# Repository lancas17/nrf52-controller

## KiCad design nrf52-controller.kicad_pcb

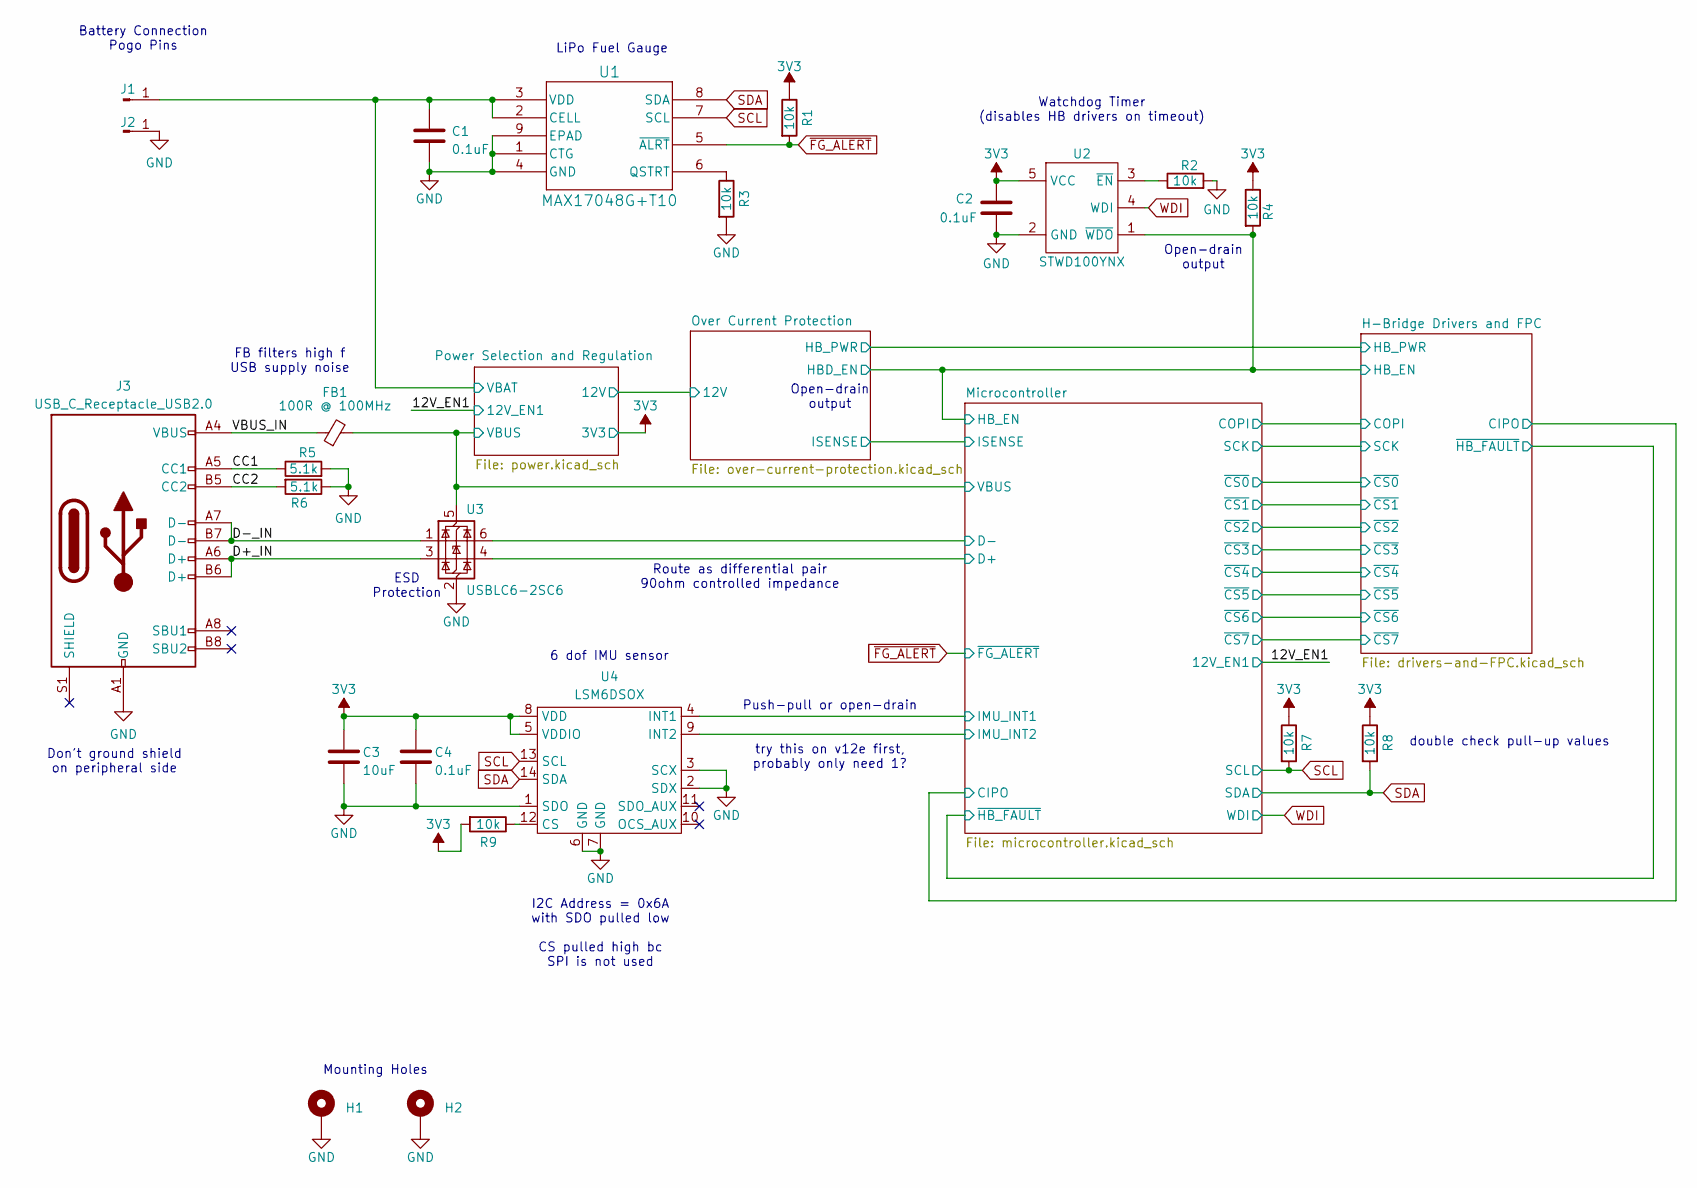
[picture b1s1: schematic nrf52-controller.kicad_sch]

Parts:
C1, C2, C4: 0.1uF; C_0402_1005Metric; JLCPCB Part # C880603
C3: 10uF; C_0402_1005Metric; JLCPCB Part # C15525
FB1: 100R @ 100MHz; C_0805_2012Metric; JLCPCB Part # C1015
H1, H2: MountingHole_Pad; MountingHole_1.8mm_M1.6_Pad_TopBottom
J1, J2: Conn_01x01_Pin; POGO_2mm-base_0.9mm-through-hole; JLCPCB Part # C5157348
J3: USB_C_Receptacle_USB2.0; USB_C_Receptacle_G-Switch_GT-USB-7010ASV; JLCPCB Part # C2988369
R1, R2, R3, R4, R7, R8, R9: 10k; R_0402_1005Metric; JLCPCB Part # C25744
R5, R6: 5.1k; R_0402_1005Metric; JLCPCB Part # C25905
U1: MAX17048G+T10; 21-0168E_T822-3_MXM; JLCPCB Part # C2682616
U2: STWD100YNX; SOT-23-5; JLCPCB Part # C1354132
U3: USBLC6-2SC6; SOT-23-6
U4: LSM6DSOX; LGA-14L_STM; JLCPCB Part # C481766

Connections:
3V3: C2.1, C3.1, C4.1, R1.1, R4.1, R7.1, R8.1, R9.2, U2.5 (VCC), U4.5 (VDDIO), U4.8 (VDD); also elsewhere on the board
/CC1: J3.A5 (CC1), R5.1
/CC2: J3.B5 (CC2), R6.2
/D+_IN: J3.A6 (D+), J3.B6 (D+), U3.3 (I/O2)
/D-_IN: J3.A7 (D-), J3.B7 (D-), U3.1 (I/O1)
/H-Bridge Drivers and FPC/HB_EN: R4.2, U2.1 (~WDO); also elsewhere on the board
/Microcontroller/D+: U3.4 (I/O2); also elsewhere on the board
/Microcontroller/D-: U3.6 (I/O1); also elsewhere on the board
/Microcontroller/IMU_INT1: U4.4 (INT1); also elsewhere on the board
/Microcontroller/IMU_INT2: U4.9 (INT2); also elsewhere on the board
/Microcontroller/VBUS: FB1.2, U3.5 (VBUS); also elsewhere on the board
/Power Selection and Regulation/VBAT: C1.1, J1.1, U1.2 (CELL), U1.3 (VDD); also elsewhere on the board
/VBUS_IN: FB1.1, J3.A4 (VBUS), J3.A9 (VBUS), J3.B4 (VBUS), J3.B9 (VBUS)
GND: C1.2, C2.2, C3.2, C4.2, H1.1, H2.1, J2.1, J3.A1 (GND), J3.A12 (GND), J3.B1 (GND), J3.B12 (GND), R2.2, R3.2, R5.2, R6.1, U1.1 (CTG), U1.4 (GND), U1.9 (EPAD), U2.2 (GND), U3.2 (GND), U4.1 (SDO), U4.2 (SDX), U4.3 (SCX), U4.6 (GND), U4.7 (GND); also elsewhere on the board
unnamed: R3.1, U1.6 (QSTRT)
unnamed: R2.1, U2.3 (~EN)
unnamed: R9.1, U4.12 (CS)
SCL: R7.2, U1.7 (SCL), U4.13 (SCL); also elsewhere on the board
SDA: R8.2, U1.8 (SDA), U4.14 (SDA); also elsewhere on the board
WDI: U2.4 (WDI); also elsewhere on the board
~FG_ALERT: R1.2, U1.5 (~ALRT); also elsewhere on the board

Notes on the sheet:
Watchdog Timer (disables HB drivers on timeout)
try this on v12e first, probably only need 1?
double check pull-up values
LiPo Fuel Gauge
ESD Protection
6 dof IMU sensor
Don't ground shield on peripheral side
Open-drain output
I2C Address = 0x6A with SDO pulled low CS pulled high bc SPI is not used
Mounting Holes
Battery Connection Pogo Pins
Route as differential pair 90ohm controlled impedance
Push-pull or open-drain
FB filters high f USB supply noise

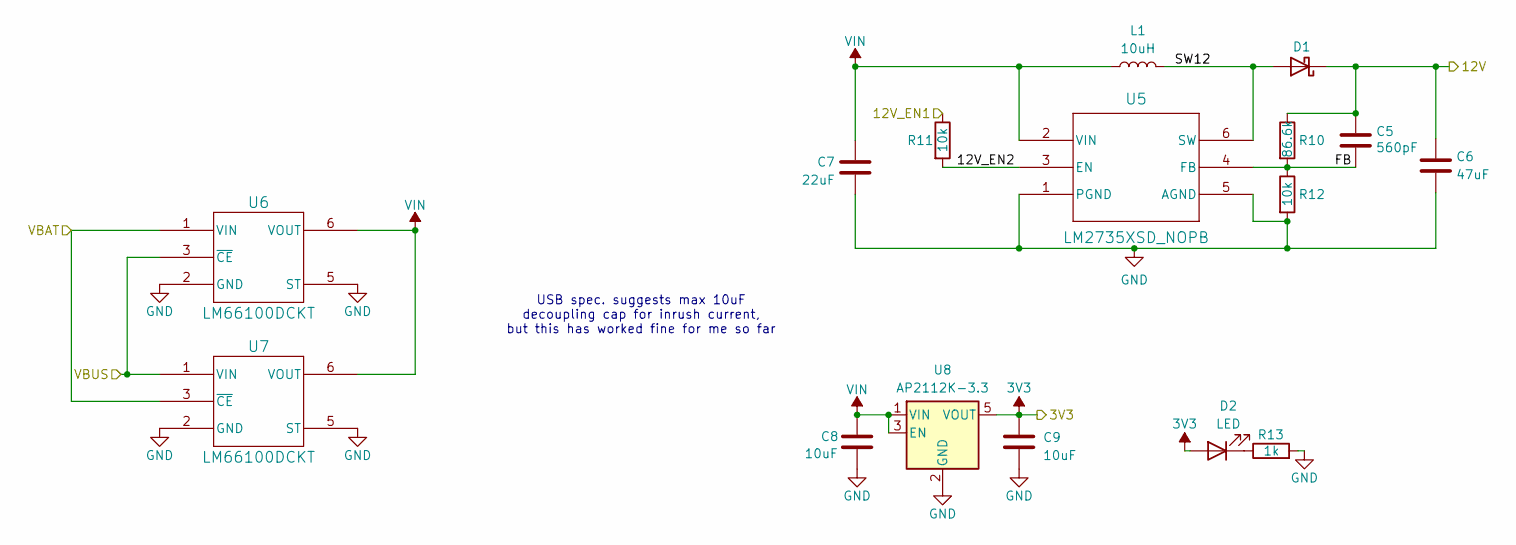
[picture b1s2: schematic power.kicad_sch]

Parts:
C5: 560pF; C_0402_1005Metric; JLCPCB Part # C464953
C6: 47uF; C_1210_3225Metric; JLCPCB Part # C77101
C7: 22uF; C_0805_2012Metric; JLCPCB Part # C45783
C8, C9: 10uF; C_0603_1608Metric; JLCPCB Part # C19702
D1: D_Schottky; D_SOD-123F; JLCPCB Part # C725481
D2: LED; LED_0603_RA_TJ-S1706CL6T5ALC9Y-A5; JLCPCB Part # C1322337
L1: 10uH; IND_357100_WRE; JLCPCB Part # C2651175
R10: 86.6k; R_0402_1005Metric; JLCPCB Part # C881092
R11, R12: 10k; R_0402_1005Metric; JLCPCB Part # C25744
R13: 1k; R_0402_1005Metric; JLCPCB Part # C11702
U5: LM2735XSD_NOPB; Texas_PWSON-N6; JLCPCB Part # C2072080
U6, U7: LM66100DCKT; SC70_DCK6_TI; JLCPCB Part # C2832141
U8: AP2112K-3.3; SOT-23-5

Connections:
3V3: C9.1, D2.2 (A), U8.5 (VOUT); also elsewhere on the board
/12V_EN1: R11.1; also elsewhere on the board
/Microcontroller/VBUS: U6.3 (~CE), U7.1 (VIN); also elsewhere on the board
/Over Current Protection/12V: C5.2, C6.2, D1.1 (K), R10.1; also elsewhere on the board
/Power Selection and Regulation/12V_EN2: R11.2, U5.3 (EN)
/Power Selection and Regulation/FB: C5.1, R10.2, R12.1, U5.4 (FB)
/Power Selection and Regulation/SW12: D1.2 (A), L1.2, U5.6 (SW)
/Power Selection and Regulation/VBAT: U6.1 (VIN), U7.3 (~CE); also elsewhere on the board
GND: C6.1, C7.2, C8.2, C9.2, R12.2, R13.2, U5.1 (PGND), U5.5 (AGND), U5.7 (EPAD), U6.2 (GND), U6.4 (NC), U6.5 (ST), U7.2 (GND), U7.4 (NC), U7.5 (ST), U8.2 (GND); also elsewhere on the board
unnamed: D2.1 (K), R13.1
VIN: C7.1, C8.1, L1.1, U5.2 (VIN), U6.6 (VOUT), U7.6 (VOUT), U8.1 (VIN), U8.3 (EN)

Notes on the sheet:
USB spec. suggests max 10uF decoupling cap for inrush current, but this has worked fine for me so far

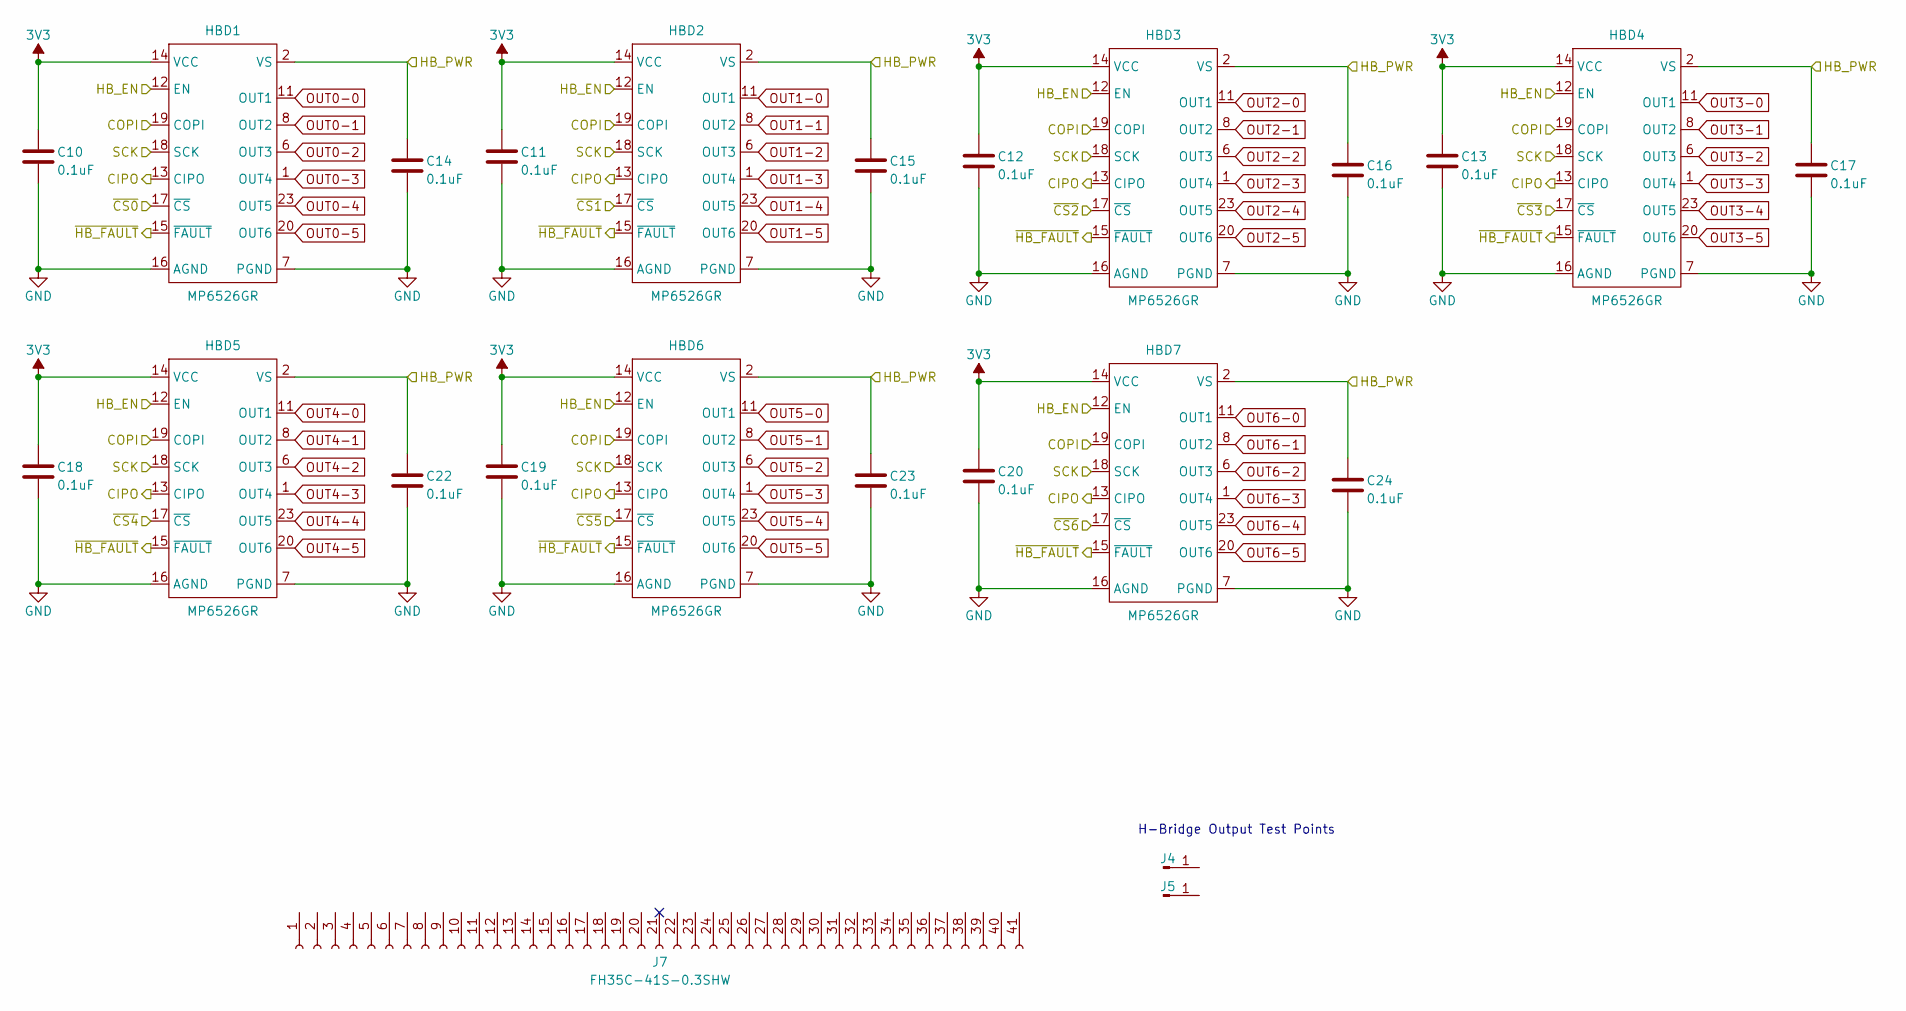
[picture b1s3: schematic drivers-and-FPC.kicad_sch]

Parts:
C10, C11, C12, C13, C14, C15, C16, C17, C18, C19, C20, C22, C23, C24: 0.1uF; C_0402_1005Metric; JLCPCB Part # C880603
HBD1, HBD2, HBD3, HBD4, HBD5, HBD6, HBD7: MP6526GR; QFN-24-1EP_4x4mm_P0.5mm_EP2.7x2.7mm
J4, J5: Conn_01x01_Pin; TP_1mm
J7: FH35C-41S-0.3SHW; CONN_FH35W-41S-0.3SHW; JLCPCB Part # C424663

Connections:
3V3: C10.1, C11.1, C12.1, C13.1, C18.1, C19.1, C20.1, HBD1.14 (VCC), HBD2.14 (VCC), HBD3.14 (VCC), HBD4.14 (VCC), HBD5.14 (VCC), HBD6.14 (VCC), HBD7.14 (VCC); also elsewhere on the board
/H-Bridge Drivers and FPC/CIPO: HBD1.13 (CIPO), HBD2.13 (CIPO), HBD3.13 (CIPO), HBD4.13 (CIPO), HBD5.13 (CIPO), HBD6.13 (CIPO), HBD7.13 (CIPO); also elsewhere on the board
/H-Bridge Drivers and FPC/COPI: HBD1.19 (COPI), HBD2.19 (COPI), HBD3.19 (COPI), HBD4.19 (COPI), HBD5.19 (COPI), HBD6.19 (COPI), HBD7.19 (COPI); also elsewhere on the board
/H-Bridge Drivers and FPC/HB_EN: HBD1.12 (EN), HBD2.12 (EN), HBD3.12 (EN), HBD4.12 (EN), HBD5.12 (EN), HBD6.12 (EN), HBD7.12 (EN); also elsewhere on the board
/H-Bridge Drivers and FPC/SCK: HBD1.18 (SCK), HBD2.18 (SCK), HBD3.18 (SCK), HBD4.18 (SCK), HBD5.18 (SCK), HBD6.18 (SCK), HBD7.18 (SCK); also elsewhere on the board
/H-Bridge Drivers and FPC/~CS0: HBD1.17 (~CS); also elsewhere on the board
/H-Bridge Drivers and FPC/~CS1: HBD2.17 (~CS); also elsewhere on the board
/H-Bridge Drivers and FPC/~CS2: HBD3.17 (~CS); also elsewhere on the board
/H-Bridge Drivers and FPC/~CS3: HBD4.17 (~CS); also elsewhere on the board
/H-Bridge Drivers and FPC/~CS4: HBD5.17 (~CS); also elsewhere on the board
/H-Bridge Drivers and FPC/~CS5: HBD6.17 (~CS); also elsewhere on the board
/H-Bridge Drivers and FPC/~CS6: HBD7.17 (~CS); also elsewhere on the board
/H-Bridge Drivers and FPC/~HB_FAULT: HBD1.15 (~FAULT), HBD2.15 (~FAULT), HBD3.15 (~FAULT), HBD4.15 (~FAULT), HBD5.15 (~FAULT), HBD6.15 (~FAULT), HBD7.15 (~FAULT); also elsewhere on the board
GND: C10.2, C11.2, C12.2, C13.2, C14.2, C15.2, C16.2, C17.2, C18.2, C19.2, C20.2, C22.2, C23.2, C24.2, HBD1.7 (PGND), HBD1.9 (PGND), HBD1.10 (PGND), HBD1.16 (AGND), HBD1.21 (PGND), HBD1.22 (PGND), HBD1.24 (PGND), HBD1.25 (EPAD), HBD2.7 (PGND), HBD2.9 (PGND), HBD2.10 (PGND), HBD2.16 (AGND), HBD2.21 (PGND), HBD2.22 (PGND), HBD2.24 (PGND), HBD2.25 (EPAD), HBD3.7 (PGND), HBD3.9 (PGND), HBD3.10 (PGND), HBD3.16 (AGND), HBD3.21 (PGND), HBD3.22 (PGND), HBD3.24 (PGND), HBD3.25 (EPAD), HBD4.7 (PGND), HBD4.9 (PGND), HBD4.10 (PGND), HBD4.16 (AGND), HBD4.21 (PGND), HBD4.22 (PGND), HBD4.24 (PGND), HBD4.25 (EPAD), HBD5.7 (PGND), HBD5.9 (PGND), HBD5.10 (PGND), HBD5.16 (AGND), HBD5.21 (PGND), HBD5.22 (PGND), HBD5.24 (PGND), HBD5.25 (EPAD), HBD6.7 (PGND), HBD6.9 (PGND), HBD6.10 (PGND), HBD6.16 (AGND), HBD6.21 (PGND), HBD6.22 (PGND), HBD6.24 (PGND), HBD6.25 (EPAD), HBD7.7 (PGND), HBD7.9 (PGND), HBD7.10 (PGND), HBD7.16 (AGND), HBD7.21 (PGND), HBD7.22 (PGND), HBD7.24 (PGND), HBD7.25 (EPAD); also elsewhere on the board
OUT0-0: HBD1.11 (OUT1)
OUT0-1: HBD1.8 (OUT2)
OUT0-2: HBD1.6 (OUT3)
OUT0-3: HBD1.1 (OUT4)
OUT0-4: HBD1.23 (OUT5)
OUT0-5: HBD1.20 (OUT6)
OUT1-0: HBD2.11 (OUT1)
OUT1-1: HBD2.8 (OUT2)
OUT1-2: HBD2.6 (OUT3)
OUT1-3: HBD2.1 (OUT4)
OUT1-4: HBD2.23 (OUT5)
OUT1-5: HBD2.20 (OUT6)
OUT2-0: HBD3.11 (OUT1)
OUT2-1: HBD3.8 (OUT2)
OUT2-2: HBD3.6 (OUT3)
OUT2-3: HBD3.1 (OUT4)
OUT2-4: HBD3.23 (OUT5)
OUT2-5: HBD3.20 (OUT6)
OUT3-0: HBD4.11 (OUT1)
OUT3-1: HBD4.8 (OUT2)
OUT3-2: HBD4.6 (OUT3)
OUT3-3: HBD4.1 (OUT4)
OUT3-4: HBD4.23 (OUT5)
OUT3-5: HBD4.20 (OUT6)
OUT4-0: HBD5.11 (OUT1)
OUT4-1: HBD5.8 (OUT2)
OUT4-2: HBD5.6 (OUT3)
OUT4-3: HBD5.1 (OUT4)
OUT4-4: HBD5.23 (OUT5)
OUT4-5: HBD5.20 (OUT6)
OUT5-0: HBD6.11 (OUT1)
OUT5-1: HBD6.8 (OUT2)
OUT5-2: HBD6.6 (OUT3)
OUT5-3: HBD6.1 (OUT4)
OUT5-4: HBD6.23 (OUT5)
OUT5-5: HBD6.20 (OUT6)
OUT6-0: HBD7.11 (OUT1)
OUT6-1: HBD7.8 (OUT2)
OUT6-2: HBD7.6 (OUT3)
OUT6-3: HBD7.1 (OUT4)
OUT6-4: HBD7.23 (OUT5)
OUT6-5: HBD7.20 (OUT6)
VS: C14.1, C15.1, C16.1, C17.1, C22.1, C23.1, C24.1, HBD1.2 (VS), HBD1.3 (VS), HBD1.4 (VS), HBD1.5 (VS), HBD2.2 (VS), HBD2.3 (VS), HBD2.4 (VS), HBD2.5 (VS), HBD3.2 (VS), HBD3.3 (VS), HBD3.4 (VS), HBD3.5 (VS), HBD4.2 (VS), HBD4.3 (VS), HBD4.4 (VS), HBD4.5 (VS), HBD5.2 (VS), HBD5.3 (VS), HBD5.4 (VS), HBD5.5 (VS), HBD6.2 (VS), HBD6.3 (VS), HBD6.4 (VS), HBD6.5 (VS), HBD7.2 (VS), HBD7.3 (VS), HBD7.4 (VS), HBD7.5 (VS); also elsewhere on the board

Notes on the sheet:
H-Bridge Output Test Points

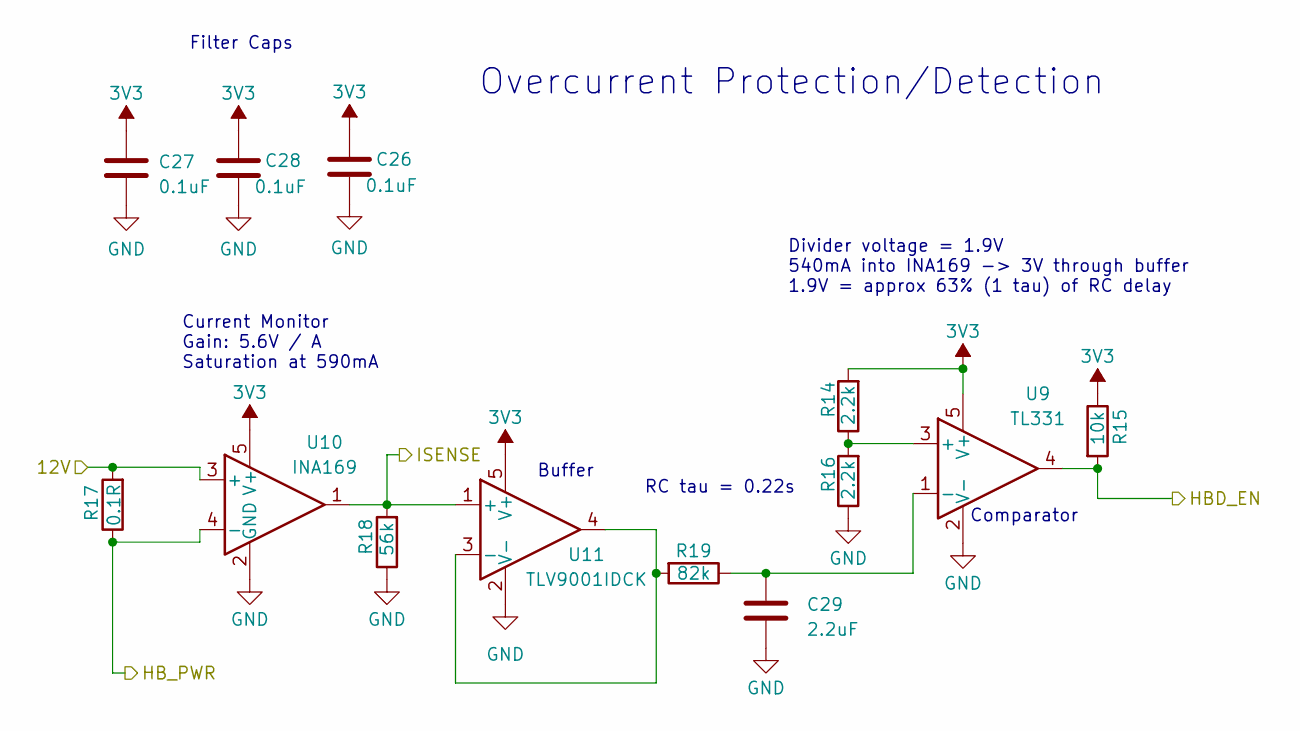
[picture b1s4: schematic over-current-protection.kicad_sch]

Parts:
C26, C27, C28: 0.1uF; C_0402_1005Metric; JLCPCB Part # C880603
C29: 2.2uF; C_0402_1005Metric; JLCPCB Part # C12530
R14, R16: 2.2k; R_0402_1005Metric; JLCPCB Part # C25879
R15: 10k; R_0402_1005Metric; JLCPCB Part # C25744
R17: 0.1R; R_1206_3216Metric; JLCPCB Part # C25334
R18: 56k; R_0402_1005Metric
R19: 82k; R_0402_1005Metric; JLCPCB Part # C4142
U9: TL331; SOT-23-5; JLCPCB Part # C2877827
U10: INA169; SOT-23-5; JLCPCB Part # C44322
U11: TLV9001IDCK; SOT-353_SC-70-5; JLCPCB Part # C398362

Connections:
3V3: C26.1, C27.1, C28.1, R14.2, R15.1, U9.5 (V+), U10.5 (V+), U11.5 (V+); also elsewhere on the board
/H-Bridge Drivers and FPC/HB_EN: R15.2, U9.4; also elsewhere on the board
/Microcontroller/ISENSE: R18.2, U10.1, U11.1 (+); also elsewhere on the board
/Over Current Protection/12V: R17.2, U10.3 (+); also elsewhere on the board
GND: C26.2, C27.2, C28.2, C29.2, R16.1, R18.1, U9.2 (V-), U10.2 (GND), U11.2 (V-); also elsewhere on the board
unnamed: R14.1, R16.2, U9.3 (+)
unnamed: C29.1, R19.1, U9.1 (-)
unnamed: R19.2, U11.3 (-), U11.4
VS: R17.1, U10.4 (-); also elsewhere on the board

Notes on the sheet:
Overcurrent Protection/Detection
Buffer
RC tau = 0.22s
Filter Caps
Divider voltage = 1.9V 540mA into INA169 -> 3V through buffer 1.9V = approx 63% (1 tau) of RC delay
Comparator
Current Monitor Gain: 5.6V / A Saturation at 590mA

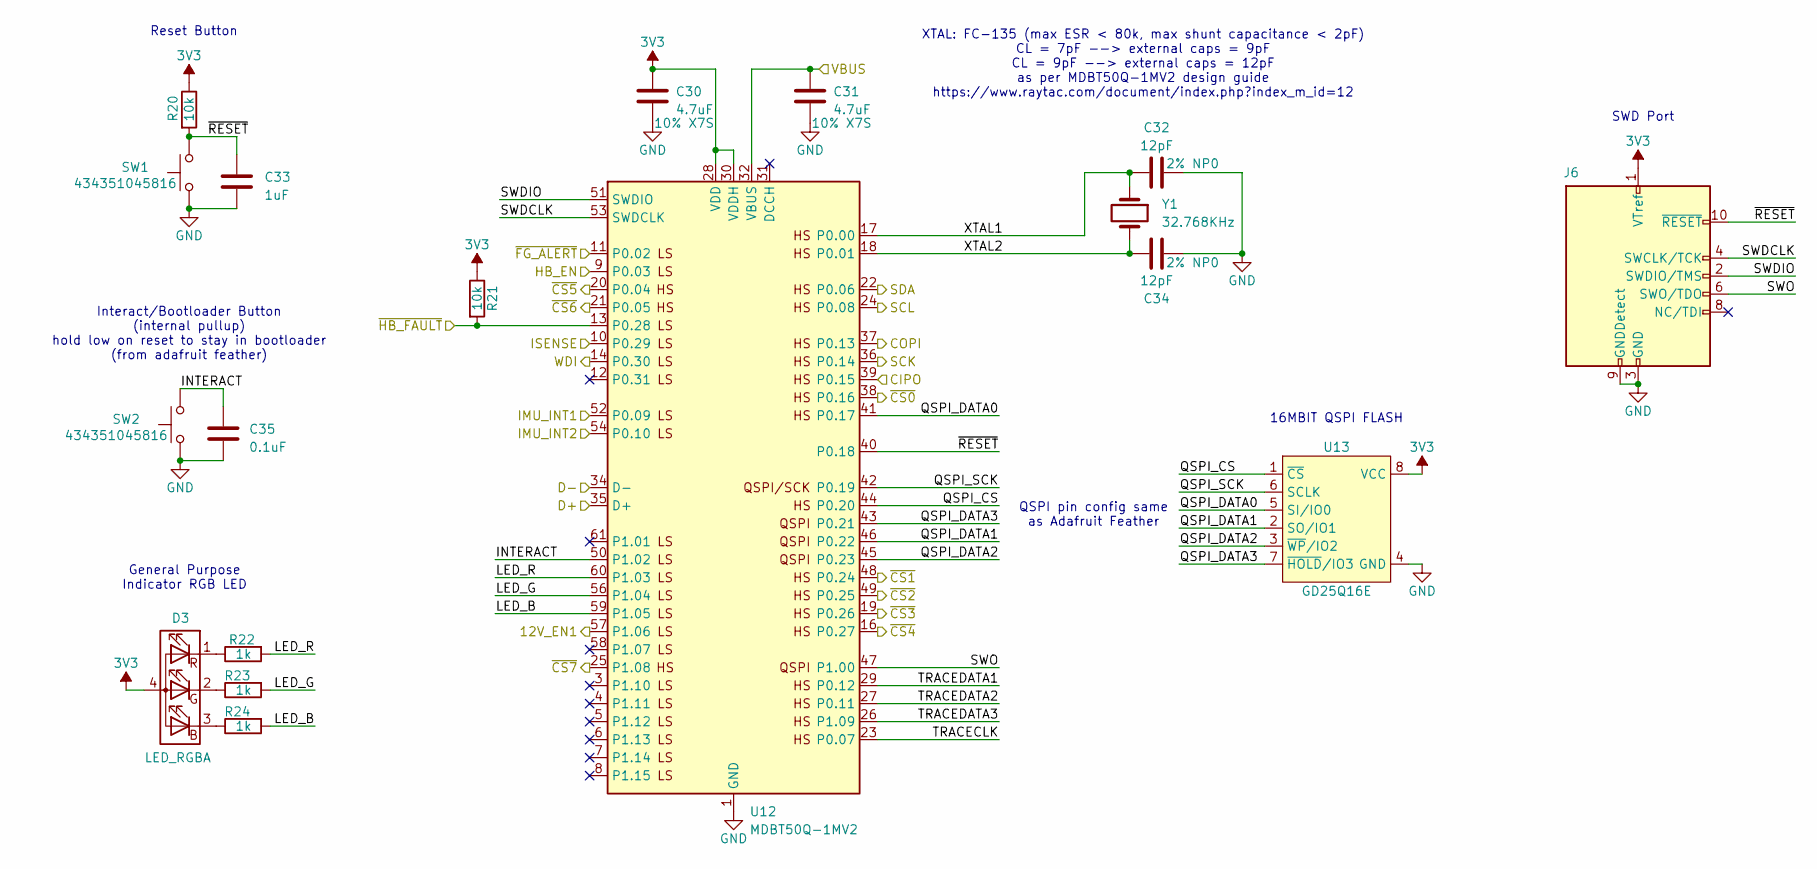
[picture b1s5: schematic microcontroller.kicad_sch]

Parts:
C30, C31: 4.7uF; C_0603_1608Metric
C32, C34: 12pF; C_0402_1005Metric
C33: 1uF; C_0402_1005Metric; JLCPCB Part # C52923
C35: 0.1uF; C_0402_1005Metric; JLCPCB Part # C880603
D3: LED_RGBA; RGBA_LTST-S310F3WT; JLCPCB Part # C284951
J6: Conn_ARM_JTAG_SWD_10; SWD_2x10_target-pads
R20, R21: 10k; R_0402_1005Metric; JLCPCB Part # C25744
R22, R23, R24: 1k; R_0402_1005Metric; JLCPCB Part # C11702
SW1, SW2: 434351045816; SW_Wurth_434351045816; JLCPCB Part # C5337107
U12: MDBT50Q-1MV2; Raytac_MDBT50Q
U13: GD25Q16E; WSON-8_3x2mm_EP-0.2x2mm
Y1: 32.768KHz; Crystal_SMD_3215-2Pin_3.2x1.5mm

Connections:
3V3: C30.1, D3.4 (A), J6.1 (VTref), R20.1, R21.1, U12.28 (VDD), U12.30 (VDDH), U13.8 (VCC); also elsewhere on the board
/12V_EN1: U12.57 (P1.06); also elsewhere on the board
/H-Bridge Drivers and FPC/CIPO: U12.39 (P0.15); also elsewhere on the board
/H-Bridge Drivers and FPC/COPI: U12.37 (P0.13); also elsewhere on the board
/H-Bridge Drivers and FPC/HB_EN: U12.9 (P0.03); also elsewhere on the board
/H-Bridge Drivers and FPC/SCK: U12.36 (P0.14); also elsewhere on the board
/H-Bridge Drivers and FPC/~CS0: U12.38 (P0.16); also elsewhere on the board
/H-Bridge Drivers and FPC/~CS1: U12.48 (P0.24); also elsewhere on the board
/H-Bridge Drivers and FPC/~CS2: U12.49 (P0.25); also elsewhere on the board
/H-Bridge Drivers and FPC/~CS3: U12.19 (P0.26); also elsewhere on the board
/H-Bridge Drivers and FPC/~CS4: U12.16 (P0.27); also elsewhere on the board
/H-Bridge Drivers and FPC/~CS5: U12.20 (P0.04); also elsewhere on the board
/H-Bridge Drivers and FPC/~CS6: U12.21 (P0.05); also elsewhere on the board
/H-Bridge Drivers and FPC/~HB_FAULT: R21.2, U12.13 (P0.28); also elsewhere on the board
/Microcontroller/D+: U12.35 (D+); also elsewhere on the board
/Microcontroller/D-: U12.34 (D-); also elsewhere on the board
/Microcontroller/IMU_INT1: U12.52 (P0.09); also elsewhere on the board
/Microcontroller/IMU_INT2: U12.54 (P0.10); also elsewhere on the board
/Microcontroller/INTERACT: C35.1, SW2.2, U12.50 (P1.02)
/Microcontroller/ISENSE: U12.10 (P0.29); also elsewhere on the board
/Microcontroller/LED_B: R24.2, U12.59 (P1.05)
/Microcontroller/LED_G: R23.2, U12.56 (P1.04)
/Microcontroller/LED_R: R22.2, U12.60 (P1.03)
/Microcontroller/QSPI_CS: U12.44 (P0.20), U13.1 (~CS)
/Microcontroller/QSPI_DATA0: U12.41 (P0.17), U13.5 (SI/IO0)
/Microcontroller/QSPI_DATA1: U12.46 (P0.22), U13.2 (SO/IO1)
/Microcontroller/QSPI_DATA2: U12.45 (P0.23), U13.3 (~WP/IO2)
/Microcontroller/QSPI_DATA3: U12.43 (P0.21), U13.7 (~HOLD/IO3)
/Microcontroller/QSPI_SCK: U12.42 (P0.19), U13.6 (SCLK)
/Microcontroller/SWDCLK: J6.4 (SWCLK/TCK), U12.53 (SWDCLK)
/Microcontroller/SWDIO: J6.2 (SWDIO/TMS), U12.51 (SWDIO)
/Microcontroller/SWO: J6.6 (SWO/TDO), U12.47 (P1.00)
/Microcontroller/TRACECLK: U12.23 (P0.07)
/Microcontroller/TRACEDATA1: U12.29 (P0.12)
/Microcontroller/TRACEDATA2: U12.27 (P0.11)
/Microcontroller/TRACEDATA3: U12.26 (P1.09)
/Microcontroller/VBUS: C31.1, U12.32 (VBUS); also elsewhere on the board
/Microcontroller/XTAL1: C32.1, U12.17 (P0.00), Y1.1
/Microcontroller/XTAL2: C34.2, U12.18 (P0.01), Y1.2
/Microcontroller/~CS7: U12.25 (P1.08)
/Microcontroller/~RESET: C33.1, J6.10 (~RESET), R20.2, SW1.2, U12.40 (P0.18)
GND: C30.2, C31.2, C32.2, C33.2, C34.1, C35.2, J6.3 (GND), J6.5 (GND), J6.9 (GNDDetect), SW1.1, SW2.1, U12.1 (GND), U12.2 (GND), U12.15 (GND), U12.33 (GND), U12.55 (GND), U13.4 (GND), U13.9 (EPAD); also elsewhere on the board
unnamed: D3.3 (BK), R24.1
unnamed: D3.2 (GK), R23.1
unnamed: D3.1 (RK), R22.1
SCL: U12.24 (P0.08); also elsewhere on the board
SDA: U12.22 (P0.06); also elsewhere on the board
WDI: U12.14 (P0.30); also elsewhere on the board
~FG_ALERT: U12.11 (P0.02); also elsewhere on the board

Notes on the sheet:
XTAL: FC-135 (max ESR < 80k, max shunt capacitance < 2pF) CL = 7pF --> external caps = 9pF CL = 9pF --> external caps = 12pF as per MDBT50Q-1MV2 design guide https://www.raytac.com/document/index.php?index_m_id=12
16MBIT QSPI FLASH
QSPI pin config same as Adafruit Feather
SWD Port
Reset Button
General Purpose Indicator RGB LED
Interact/Bootloader Button (internal pullup) hold low on reset to stay in bootloader (from adafruit feather)

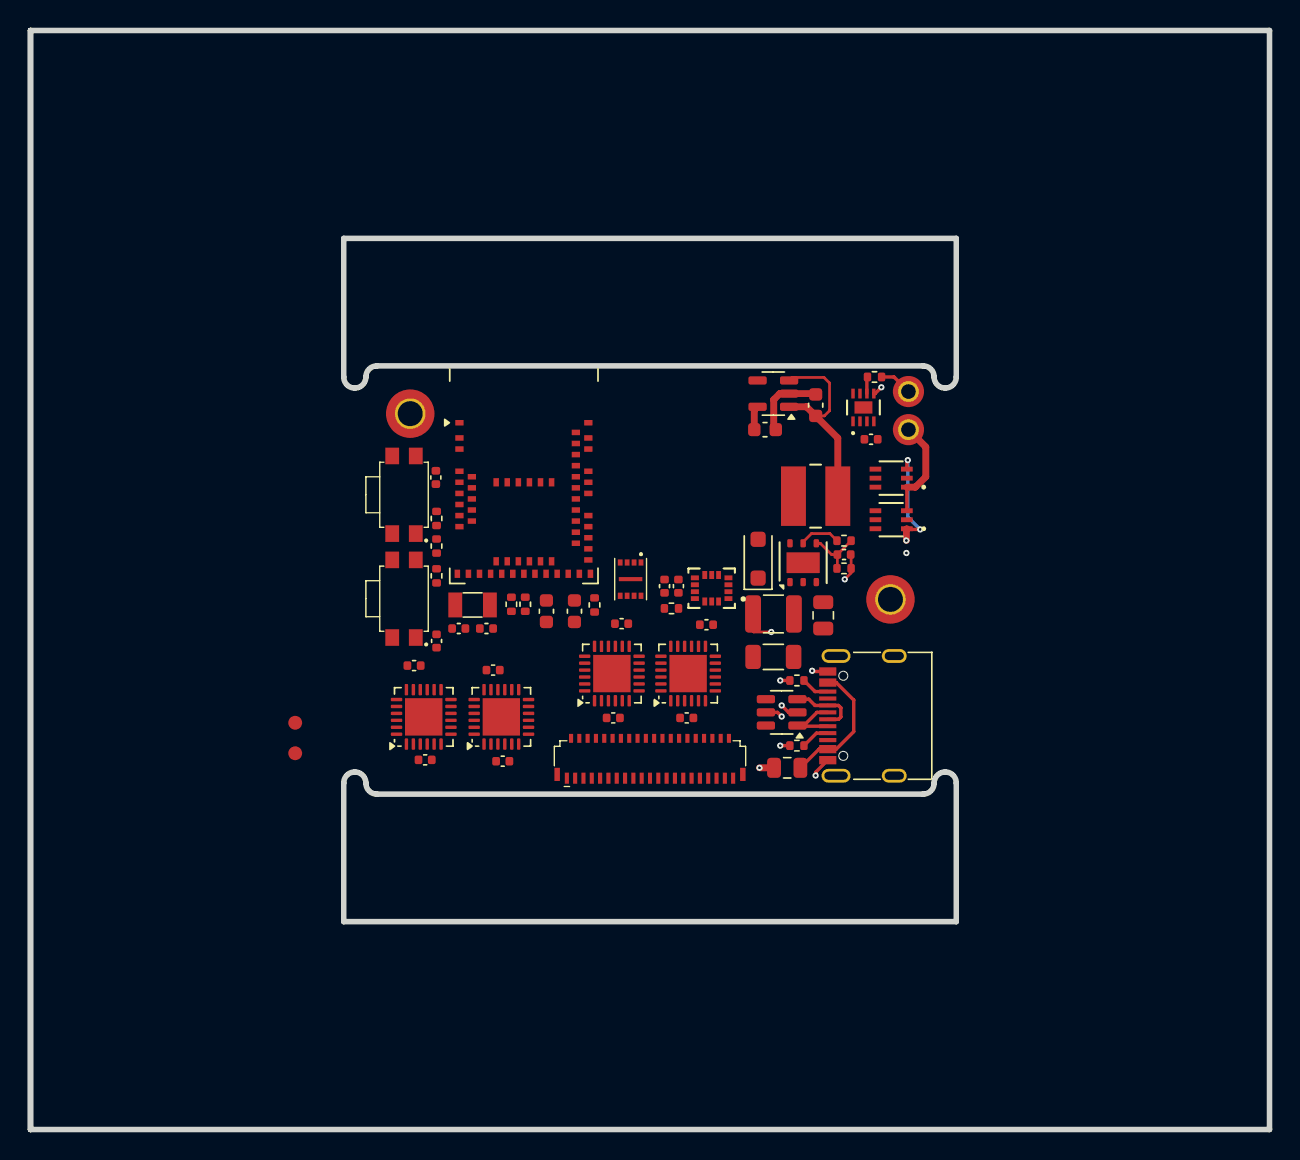
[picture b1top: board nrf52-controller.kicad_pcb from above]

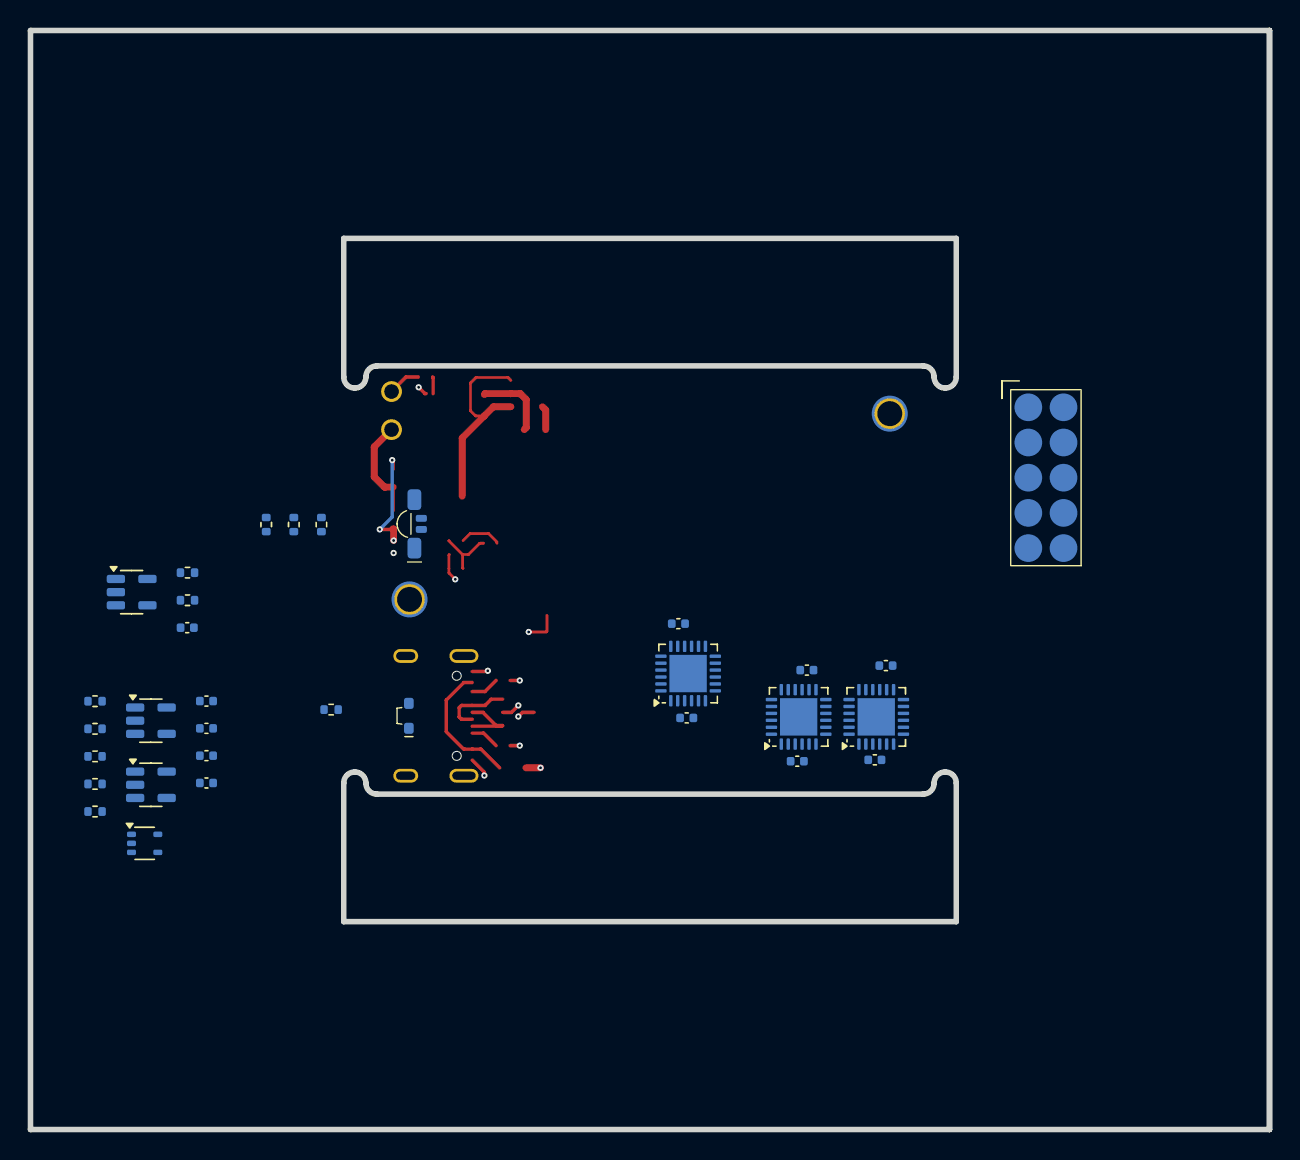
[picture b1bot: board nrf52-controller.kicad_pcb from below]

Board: 8 copper layers, 89.4 x 79.3 mm, 94 parts (32 on the bottom side), 63 nets.

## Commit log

2024-04-11 initial commit - sch draft WIP
2024-04-13 schematic rough draft except fpc
2024-04-13 schematic draft 2; no FPC connections, no testpoints
2024-04-16 layout start
2024-05-02 separated smaller board layout variant
2024-05-02 add ds_store to gitignore
